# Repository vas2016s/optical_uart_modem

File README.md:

# optical_uart_modem

! проект находится в зачаточном состоянии, работоспособность не гарантирована

Оптический модем предназначен для передаи информации формата uart через водную или воздушную среду при помощи светового сигнала.

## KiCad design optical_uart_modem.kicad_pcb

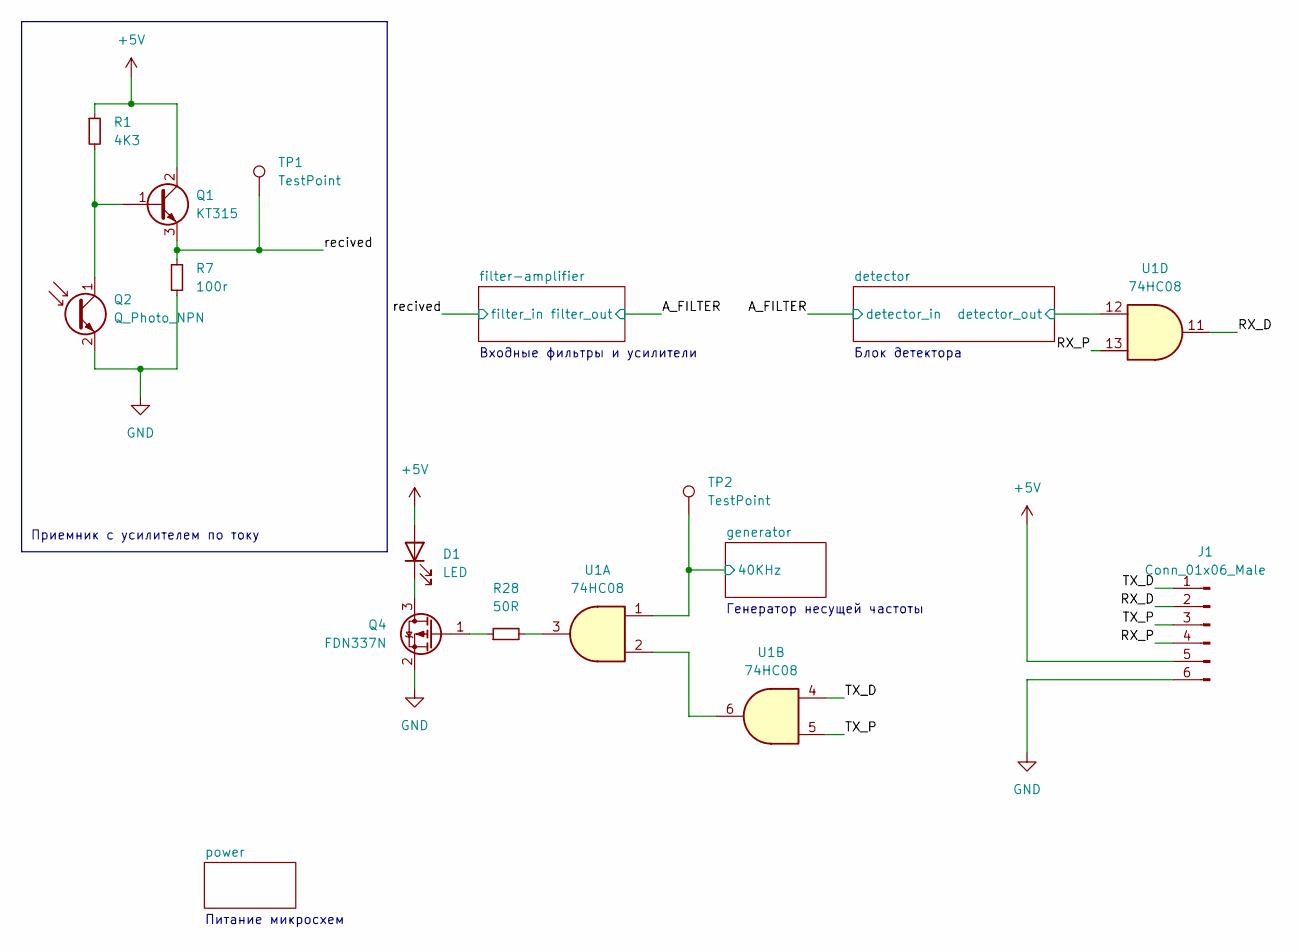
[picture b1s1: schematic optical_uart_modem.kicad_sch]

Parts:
D1: LED; PinHeader_1x02_P2.54mm_Vertical
J1: Conn_01x06_Male; PinHeader_1x06_P2.54mm_Vertical
Q1: KT315; PinHeader_1x03_P2.54mm_Vertical
Q2: Q_Photo_NPN; PinHeader_1x02_P2.54mm_Vertical
Q4: FDN337N; SOT-23
R1: 4K3; R_0603_1608Metric
R7: 100r; R_0603_1608Metric
R28: 50R; R_0603_1608Metric
TP1, TP2: TestPoint; TestPoint_Pad_D1.0mm
U1: 74HC08; SO-14_3.9x8.65mm_P1.27mm

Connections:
+5V: D1.2 (A), J1.5, Q1.2 (C), R1.1; also elsewhere on the board
/RX_D: J1.2, U1.11
/RX_P: J1.4, U1.13
/TX_D: J1.1, U1.4
/TX_P: J1.3, U1.5
/detector/detector_out: U1.12; also elsewhere on the board
/generator/40KHz: TP2.1, U1.1; also elsewhere on the board
/recived: Q1.3 (E), R7.1, TP1.1; also elsewhere on the board
GND: J1.6, Q2.2 (E), Q4.2 (S), R7.2; also elsewhere on the board
unnamed: D1.1 (K), Q4.3 (D)
unnamed: Q1.1 (B), Q2.1 (C), R1.2
unnamed: Q4.1 (G), R28.1
unnamed: R28.2, U1.3
unnamed: U1.2, U1.6

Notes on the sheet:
Питание микросхем
Приемник с усилителем по току
Генератор несущей частоты
Входные фильтры и усилители
Блок детектора

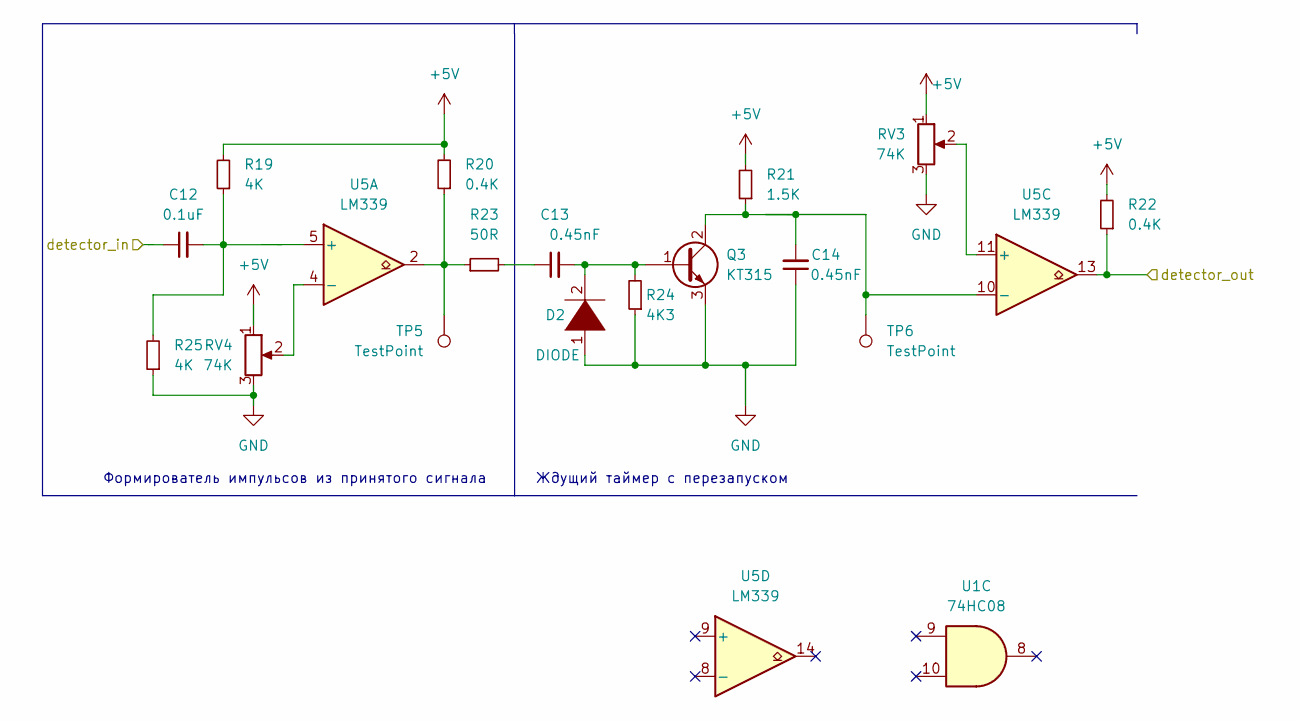
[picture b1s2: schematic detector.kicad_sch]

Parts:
C12: 0.1uF; C_0603_1608Metric
C13, C14: 0.45nF; C_0603_1608Metric
D2: DIODE; PinHeader_1x02_P2.54mm_Vertical
Q3: KT315; PinHeader_1x03_P2.54mm_Vertical
R19, R25: 4K; R_0603_1608Metric
R20, R22: 0.4K; R_0603_1608Metric
R21: 1.5K; R_0603_1608Metric
R23: 50R; R_0603_1608Metric
R24: 4K3; R_0603_1608Metric
RV3, RV4: 74K; Potentiometer_Bourns_3296W_Vertical
TP5, TP6: TestPoint; TestPoint_Pad_D1.0mm
U1: 74HC08; SO-14_3.9x8.65mm_P1.27mm
U5: LM339; SO-14_3.9x8.65mm_P1.27mm

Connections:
+5V: R19.2, R20.2, R21.2, R22.2, RV3.1, RV4.1; also elsewhere on the board
/A_FILTER: C12.1; also elsewhere on the board
/detector/detector_out: R22.1, U5.13; also elsewhere on the board
GND: C14.1, D2.1 (K), Q3.3 (E), R24.1, R25.1, RV3.3, RV4.3; also elsewhere on the board
unnamed: C12.2, R19.1, R25.2, U5.5 (+)
unnamed: C13.1, R23.2
unnamed: C13.2, D2.2 (A), Q3.1 (B), R24.2
unnamed 25: C14.2, Q3.2 (C), R21.1, TP6.1, U5.10 (-); also elsewhere on the board
unnamed: R20.1, R23.1, TP5.1, U5.2
unnamed: RV3.2, U5.11 (+)
unnamed: RV4.2, U5.4 (-)

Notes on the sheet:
Ждущий таймер с перезапуском
Формирователь импульсов из принятого сигнала

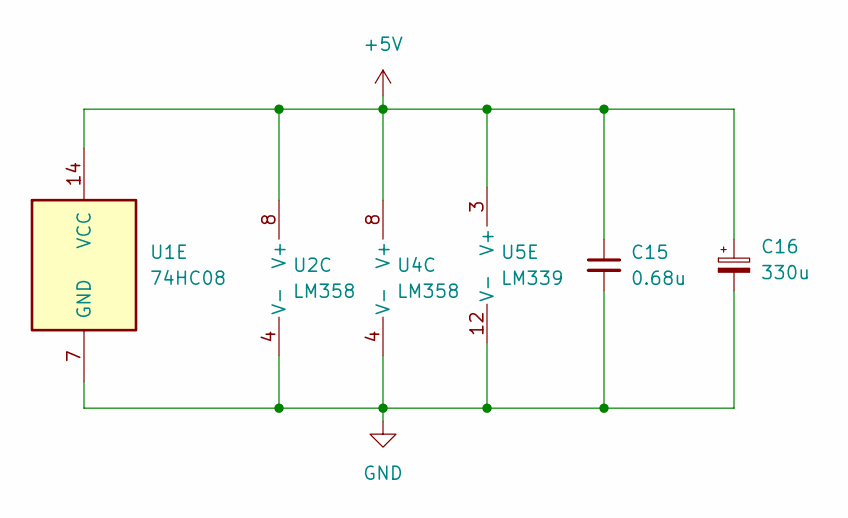
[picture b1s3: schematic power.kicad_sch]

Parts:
C15: 0.68u; C_0603_1608Metric
C16: 330u; CP_Elec_8x10.5
U1: 74HC08; SO-14_3.9x8.65mm_P1.27mm
U2, U4: LM358; SO-8_3.9x4.9mm_P1.27mm
U5: LM339; SO-14_3.9x8.65mm_P1.27mm

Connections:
+5V: C15.1, C16.1, U1.14 (VCC), U2.8 (V+), U4.8 (V+), U5.3 (V+); also elsewhere on the board
GND: C15.2, C16.2, U1.7 (GND), U2.4 (V-), U4.4 (V-), U5.12 (V-); also elsewhere on the board

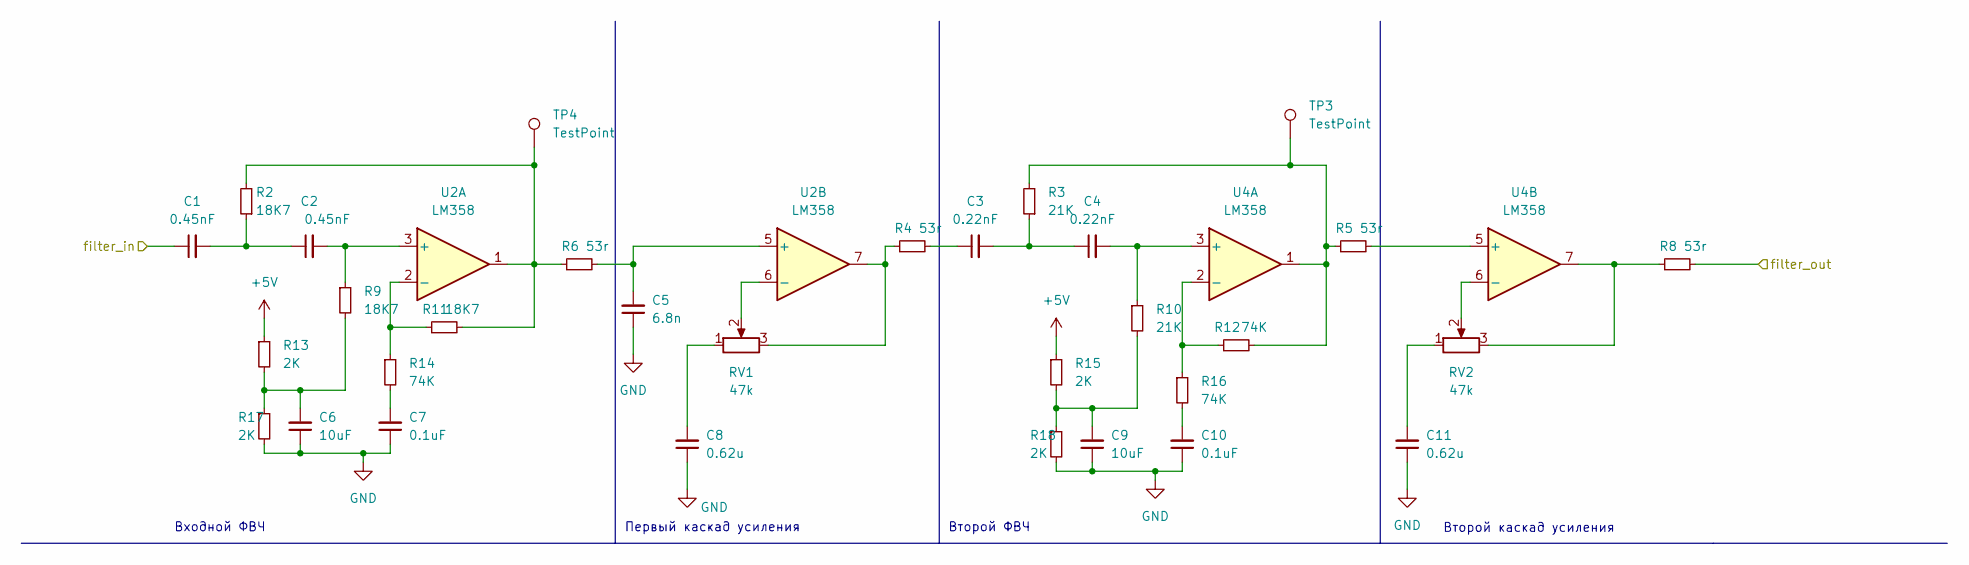
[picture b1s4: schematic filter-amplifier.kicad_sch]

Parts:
C1, C2: 0.45nF; C_0603_1608Metric
C3, C4: 0.22nF; C_0603_1608Metric
C5: 6.8n; C_0603_1608Metric
C6, C9: 10uF; C_0603_1608Metric
C7, C10: 0.1uF; C_0603_1608Metric
C8, C11: 0.62u; C_0603_1608Metric
R2, R9, R11: 18K7; R_0603_1608Metric
R3, R10: 21K; R_0603_1608Metric
R4, R5, R6, R8: 53r; R_0603_1608Metric
R12, R14, R16: 74K; R_0603_1608Metric
R13, R15, R17, R18: 2K; R_0603_1608Metric
RV1, RV2: 47k; Potentiometer_Bourns_3296W_Vertical
TP3, TP4: TestPoint; TestPoint_Pad_D1.0mm
U2, U4: LM358; SO-8_3.9x4.9mm_P1.27mm

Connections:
+5V: R13.1, R15.1; also elsewhere on the board
/A_FILTER: R8.2; also elsewhere on the board
/recived: C1.1; also elsewhere on the board
GND: C5.1, C6.1, C7.1, C8.1, C9.1, C10.1, C11.1, R17.2, R18.2; also elsewhere on the board
unnamed: C1.2, C2.1, R2.1
unnamed: C2.2, R9.1, U2.3 (+)
unnamed: C3.1, R4.2
unnamed: C3.2, C4.1, R3.1
unnamed: C4.2, R10.1, U4.3 (+)
unnamed: C5.2, R6.2, U2.5 (+)
unnamed: C6.2, R9.2, R13.2, R17.1
unnamed: C7.2, R14.2
unnamed: C8.2, RV1.1
unnamed: C9.2, R10.2, R15.2, R18.1
unnamed: C10.2, R16.2
unnamed: C11.2, RV2.1
unnamed: R4.1, RV1.3, U2.7
unnamed: R5.2, U4.5 (+)
unnamed: R8.1, RV2.3, U4.7
unnamed: R11.1, R14.1, U2.2 (-)
unnamed 35: R2.2, R6.1, R11.2, TP4.1, U2.1; also elsewhere on the board
unnamed: R12.1, R16.1, U4.2 (-)
unnamed 37: R3.2, R5.1, R12.2, TP3.1, U4.1; also elsewhere on the board
unnamed: RV1.2, U2.6 (-)
unnamed: RV2.2, U4.6 (-)

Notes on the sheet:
Первый каскад усиления
Второй ФВЧ
Входной ФВЧ
Второй каскад усиления

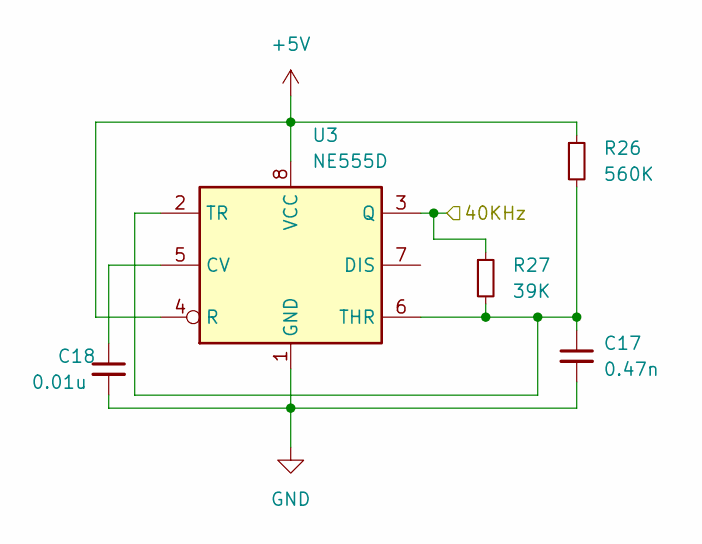
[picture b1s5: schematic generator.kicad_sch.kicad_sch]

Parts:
C17: 0.47n; C_0603_1608Metric
C18: 0.01u; C_0603_1608Metric
R26: 560K; R_0603_1608Metric
R27: 39K; R_0603_1608Metric
U3: NE555D; SOIC-8_3.9x4.9mm_P1.27mm

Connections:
+5V: R26.1, U3.4 (R), U3.8 (VCC); also elsewhere on the board
/generator/40KHz: R27.1, U3.3 (Q); also elsewhere on the board
GND: C17.2, C18.2, U3.1 (GND); also elsewhere on the board
unnamed: C17.1, R26.2, R27.2, U3.2 (TR), U3.6 (THR)
unnamed: C18.1, U3.5 (CV)

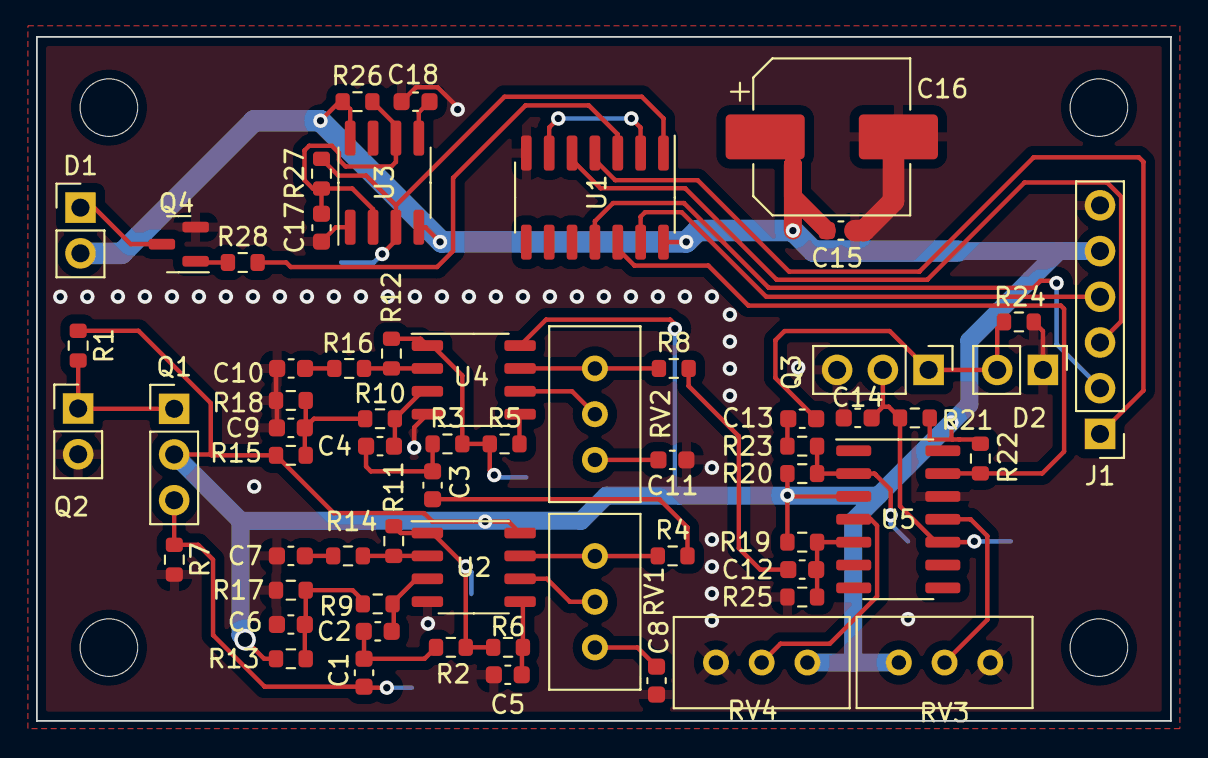
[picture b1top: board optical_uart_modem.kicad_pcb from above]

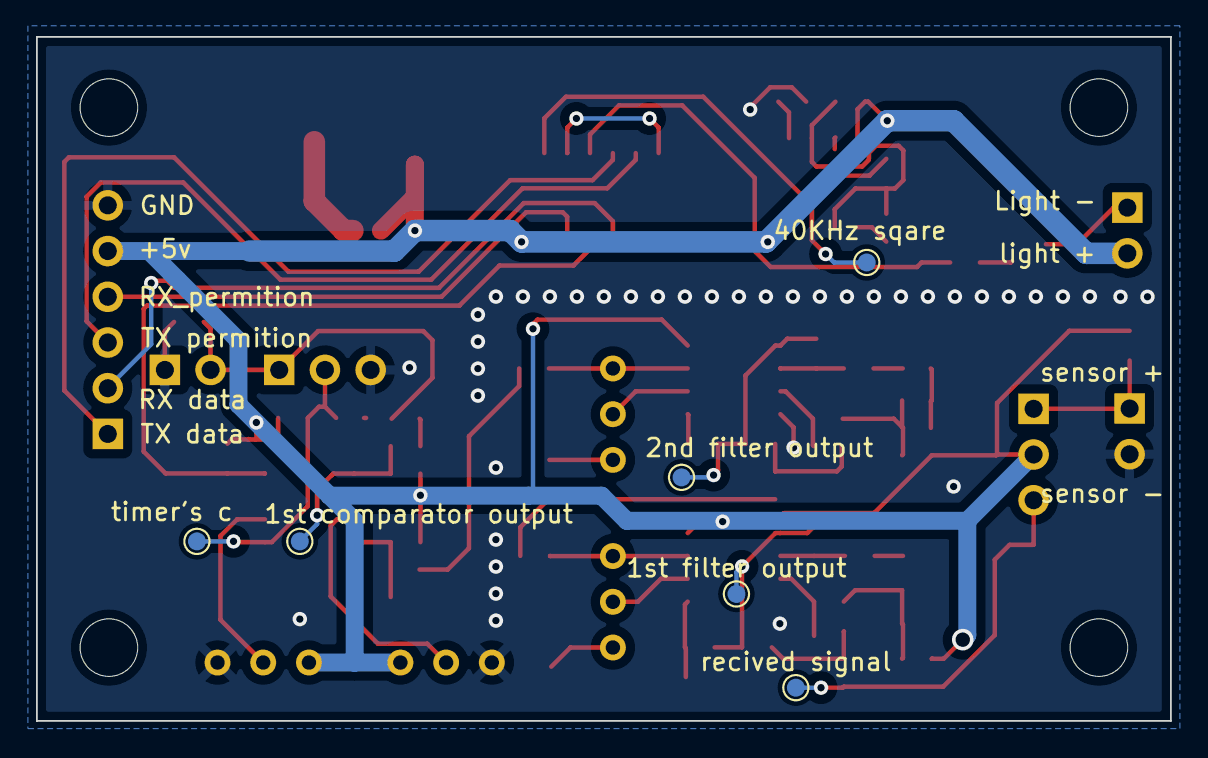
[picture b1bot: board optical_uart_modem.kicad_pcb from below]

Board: 2 copper layers, 63.0 x 38.0 mm, 68 parts (6 on the bottom side), 45 nets.

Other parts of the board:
1st comparator output, 1st filter output, 2nd filter output, 40KHz sqare: TestPoint; TestPoint_Pad_D1.0mm
recived signal: TestPoint; TestPoint_Pad_D1.0mm
timer's c: TestPoint; TestPoint_Pad_D1.0mm

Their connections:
/generator/40KHz: 40KHz sqare.1; also elsewhere on the board
/recived: recived signal.1; also elsewhere on the board
unnamed 25: timer's c.1; also elsewhere on the board
unnamed 35: 1st filter output.1; also elsewhere on the board
unnamed 37: 2nd filter output.1; also elsewhere on the board

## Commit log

2023-01-04 initial commit, 1st revision of files added
2023-01-04 some garbage removed
2023-01-04 some mistakes corrected
2023-01-05 test points and some silk added
2023-01-05 Create README.md
    Readme added
2023-01-16 values corrected, 40KHz generator modified
2023-01-16 polygons error fixed
